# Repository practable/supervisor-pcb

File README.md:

# Remote Labs Supervisor PCB V1.2
NOTE: This project has been continued in a new location, please see: [rl-supervisor-two](https://github.com/practable/rl-supervisor-two) for the latest version of this project

## Project Brief - [Remote Labs Supervisor PCB V1.2]
Design a PCB to provide power to remote labs experiments, which involve students programming microcontrollers remotely. PCB should also provide a supervisory role, blocking actuation of experimental hardware if it is likely to cause damage to the equipment. <br> <br>

This allows students to upload their own code to a bare bones microcontroller, without risk of causing hardware damage or unsafe conditions. <br>

# Using Remote Labs Supervisor PCB 

_This document is intended to be a useage guide for the Remote Labs Supervisor PCB, and document the different use cases and configurations it is capable of._

For coded examples of the various features please see [PCB Unit Tests](https://github.com/ImogenWren/RemoteLabs_Supervisor_PCB/tree/main/Verification%20Tests/PCB%20Unit%20Tests), which contains
arduino code firmware used during testing all hardware features of the PCB.

For the purposes of this document, it is assumed that the Motherboard PCB is populated with both Arduino Nano IoT 33 Daughterboards __(A1 & A2)__, with shift registers installed, and NOT the bare bones SAMD21 MCU.
A seperate document will be provided for cases in which SAMD21 MCUs are mounted to the motherboard directly.

### Pin Naming and Shift Registers

_All MCU pins will be referenced by the Arduino Pin Numbers in this document. 
Additional pins are sourced via Shift Registers attached to each MCU.
Shift Register pins are labelled as Q0 - Q7.
Both MCU connections to their independent shift registers are detailed below._

MCU Pin |  Shift Register Function 	|
---		| ---						|
D8		| LATCH	(Write to Register)	|
D11		| MOSI (Data)				|
D13		| SCK						|

_Complete pinout diagrams for both MCUs and Shift Registers can be found at the bottom of this document_

### Powering the System

The System should be provided 12v DC power via the yellow XT60 connector __J3__. The system is specified to draw a maximum of ~ 8A depending on experiment configuration, ensure that power supply selected is sufficient for specific use case.

Diode D6 (Blue) will light to show correct polarity power is provided to input.
Diode D7 (Orange) will light to show 3V3 DC power is available to microcontrollers and periferal devices.

Motherboard has reverse polarity protection, however care should be taken to ensure correct orientation of power input. - NOTE: Currently missing protection diode- awaiting delivery

### Programming the MCUs

Each MCU, supervisor and student are able to be programmed via the USB connector on the daughterboard, or via UART using the 5 pin headers __J26 Student_Prog_Header__, and __J1 Super_Prog_header__.

For UART Programming, a hat is provided for raspi GPIO pins. 5 pin cable should be connected from Raspi hat to UART Programming connector on motherboard.

__The USB connectors mounted to the __Motherboard__ should not be used if Arduino Development boards are installed, and are UNTESTED for use with bare bones MCUs installed__

-----

## Use Case 1 [Spinner Experiment]

_In this configuration the following modules should be mounted to the motherboard:_

- Infineon DC Motor Control Shield - A3

_In this configuration the following external hardware should be connected as follows:_

- DC Motor, wired to the OUTER two pins on __J18 DC Motor Output__
- Optical Encoder, plugged into __J25 Optical Encoder__

### Using the DC Motor

DC Motor PWM is routed to Infineon DC Motor Controller module via the following logic:

If MOTOR_DIR_A is driven HIGH, PWM is routed from STUDENT_MOTOR_PWM or SUPERVISOR_MOTOR_PWM to MOTOR_OUT_1
If MOTOR_DIR_B is driven HIGH, PWM is routed from STUDENT_MOTOR_PWM or SUPERVISOR_MOTOR_PWM to MOTOR_OUT_2

Care must be taken to avoid driving MOTOR_DIR_A and MOTOR_DIR_B to HIGH at the same time as this will cause shoot through.

In Order to avoid shoot through condition, Student does not have direct input to MOTOR_DIR_A or MOTOR_DIR_B. These outputs are spoofed via the Supervisor MCU.

The MCU able to pass PWM signal to Motor Control Module is selected by MCU_MOTOR_SELECT pin. When HIGH - STUDENT_MOTOR_PWM is active, when LOW - SUPERVISOR_MOTOR_PWM is active.

In order to enable the DC Motor Control Module, OUT_M_ENABLE must also be set HIGH. This is routed from either MCU using the same logic as above, when MCU_MOTOR_SELECT is HIGH, ENABLE is routed from STUDENT_MOTOR_EN, when it is set LOW, ENABLE is routed from SUPERVISOR_MOTOR_EN.

M_I_SENSE_1 and M_I_SENSE_2 output is buffered and distributed to both MCUs.

### Supervisor MCU

Supervisor MCU uses the following table for DC Motor Control:

MCU 		|Pin 	| Pin Name 		| State 		| Motor Behaviour 		| Notes
---			|---	|---			|---			|---					|---
SUPERVISOR 	|D12 	|MOTOR_DIR_1	| HIGH or LOW	| Sets motor Direction	| IF(D7 == HIGH){D12 MUST = LOW)
SUPERVISOR	|D7		|MOTOR_DIR_2	| LOW or HIGH 	| Sets motor Direction 	| IF(D12 == HIGH){D7 MUST = LOW)
SUPERVISOR	|Q0		|DC_MOTOR_EN	| HIGH			| Enables DC Motor Drive|
SUPERVISOR	|Q1		|STUDENT_M_EN	| LOW			| Blocks Student Control, Enables Supervisor Control| 
SUPERVISOR	|A7		|DC_MOTOR_IS1	| ANALOG INPUT	| Current Draw and Fault Condition Detection| 
SUPERVISOR	|A6		|DC_MOTOR_IS2	| ANALOG INPUT	| Current Draw and Fault Condition Detection| 

### Student MCU

Student MCU uses the following table for DC Motor Control: *Note - Student control relys on specific pin configurations of Supervisor MCU*

MCU 		|Pin 	| Pin Name 		| State 		| Motor Behaviour 		| Notes
---			|---	|---			|---			|---					|---
STUDENT 	|D12 	|MOTOR_DIR_1	| HIGH or LOW	| Detected by Supervisor PIN A1	| IF(D7 == HIGH){D12 MUST = LOW)
STUDENT		|D7		|MOTOR_DIR_2	| LOW or HIGH 	| Detected by Supervisor PIN A0	| IF(D12 == HIGH){D7 MUST = LOW)
STUDENT		|Q0		|DC_MOTOR_EN	| HIGH			| Enables DC Motor Drive|
SUPERVISOR	|Q1		|STUDENT_M_EN	| HIGH			| Blocks Supervisor Control, Enables Student Control| 
SUPERVISOR	|A1		|STDNT_DC_M_DIR_1| DIGITAL INPUT| Detects state of Student Direction Pin and Spoofs output if logic != illegal
SUPERVISOR	|A0		|STDNT_DC_M_DIR_2| DIGITAL INPUT| Detects state of Student Direction Pin and Spoofs output if logic != illegal
SUPERVISOR 	|D12 	|MOTOR_DIR_1	| HIGH or LOW	| Sets motor Direction - Spoofed from A1	| 
SUPERVISOR	|D7		|MOTOR_DIR_2	| LOW or HIGH 	| Sets motor Direction - Spoofed from A0	| 
STUDENT		|A7		|DC_MOTOR_IS1	| ANALOG INPUT	| Current Draw and Fault Condition Detection| 
STUDENT		|A6		|DC_MOTOR_IS2	| ANALOG INPUT	| Current Draw and Fault Condition Detection| 

### Using the Optical Encoder

_Optical encoder signals are buffered and provided to both MCUs simaltaniously, therefore getting useful data from Optical Encoder is the same process for both MCUs_

MCUs use the following table for Optical Encoder detection:

MCU 		|Pin 	| Pin Name 		| State 								| Notes
---			|---	|---			|---									|---
Both	 	|D2 	|ENCODER_B		| EXTERNAL INTERRUPT / DIGITAL INPUT	| For best performance, External Interrupt used for edge detection of Encoder waveform
Both		|D3		|ENCODER_A		| EXTERNAL INTERRUPT / DIGITAL INPUT 	| Alternative pin for External Interrupt.
Both		|D4		|ENCODER_INDEX	| DIGITAL INPUT							| Used to track center detent of optical encoder (Untested in software)

-----

## Use Case 2 [Governer Experiment]

In this configuration the following modules should be mounted to the motherboard:

- Infineon DC Motor Control Shield 	- A3
- DRV8825 Stepper Motor Driver		- A4

___DC Motor & Optical Encoder are accessed as Use Case 1 above___

In this configuration the following external hardware should be connected as follows:

- DC Motor, wired to the OUTER two pins on __J18 DC Motor Output__
- Stepper Motor, plugged into __J19 Stepper Motor Output__
- Optical Encoder, plugged into __J25 Optical Encoder__
- Limit Switch, plugged into __J23 limit_switch_A__

### Using the Stepper Motor

Stepper Motor Driver inputs are routed via the following logic:

When MCU_STEP_SELECT is HIGH, inputs are routed from STUDENT MCU. When MCU_STEP_SELECT is LOW, inputs are routed from SUPERVISOR MCU.

STEPP_EN is driven from Supervisor MCU Only, however does not seem to have any effect on stepper motor function. - Requires further investigation.

STEPPR_FAULT output is buffered and distributed to both MCUs.

LIMIT_1 Limit switch input is buffered and distributed to both MCUs.

### Supervisor MCU

Supervisor MCU uses the following table for Stepper Motor Control:

MCU 		|Pin 	| Pin Name 		| State 		| Motor Behaviour 									| Notes
---			|---	|---			|---			|---												|---
SUPERVISOR 	|D6 	|STEPP_STEP		| PULSE			| Motor advances 1 step per pulse					| 
SUPERVISOR	|Q2		|STUDENT_STEP_EN| LOW			| Blocks Student Control, Enables Supervisor Control| 
SUPERVISOR	|Q4		|STEPP_DIR		| HIGH or LOW	| Sets Stepper Motor Direction						|
SUPERVISOR	|Q5		|STEPP_SLP		| HIGH or LOW	| Enables and Sleeps motor to avoid overheating 	| MUST BE HIGH? to enable					| 
SUPERVISOR	|Q6		|STEPP_RST		| HIGH or LOW	| Resets controller board after fault condition 	| MUST BE HIGH? to enable					| 
SUPERVISOR	|Q7		|STEPP_EN		| HIGH or LOW	| Enables motor driver board						| NO DECERNABLE EFFECT? - Needs Testing		| 
SUPERVISOR	|A5		|STEPP_FLT		| DIGITAL INPUT	| Fault reporting from Stepper Control daughterboard| HIGH = NO FAULT, LOW = FAULT 				| 
SUPERVISOR	|A4		|LIMIT_1		| DIGITAL INPUT	| Limit Switch Detection.							| LOW = Switch Pressed 						| 

### Student MCU

Student MCU uses the following table for Stepper Motor Control: *Note - Student control relys on specific pin configurations of Supervisor MCU*

MCU 		|Pin 	| Pin Name 		| State 		| Motor Behaviour 									| Notes
---			|---	|---			|---			|---												|---
STUDENT 	|D6 	|STEPP_STEP		| PULSE			| Motor advances 1 step per pulse					| 
SUPERVISOR	|Q2		|STUDENT_STEP_EN| HIGH			| Enables Student Control, Blocks Supervisor Control| 
STUDENT 	|Q4		|STEPP_DIR		| HIGH or LOW	| Sets Stepper Motor Direction						|
STUDENT		|Q5		|STEPP_SLP		| HIGH or LOW	| Enables and Sleeps motor to avoid overheating 	| MUST BE HIGH? to enable					| 
STUDENT		|Q6		|STEPP_RST		| HIGH or LOW	| Resets controller board after fault condition 	| MUST BE HIGH? to enable					| 
SUPERVISOR	|Q7		|STEPP_EN		| HIGH or LOW	| Enables motor driver board						| NO DECERNABLE EFFECT? - Needs Testing		| 
STUDENT		|A5		|STEPP_FLT		| DIGITAL INPUT	| Fault reporting from Stepper Control daughterboard| HIGH = NO FAULT, LOW = FAULT 				| 
STUDENT		|A4		|LIMIT_1		| DIGITAL INPUT	| Limit Switch Detection.							| LOW = Switch Pressed 						|

#### Additional Stepper Motor Functions

SW1 - Stepper Mode Dipswitches set number of steps per revolution. If UNPOPULATED setting is at MAX RESOLUTION. (1, 1, 1 ) logic for MODE inputs.

-----

## Use Case 3 [Digger Experiment]

In this configuration the following modules should be mounted to the motherboard:

- Infineon DC Motor Control Shield 	- A3

___DC Motor & Optical Encoder are accessed as Use Case 1 above___

In this configuration the following external hardware should be connected as follows:

- DC Motor, wired to the OUTER two pins on __J18 DC Motor Output__
- Optical Encoder, plugged into __J25 Optical Encoder__
- Limit Switch, plugged into __J23 limit_switch_A__
- Servo, plugged into __J20 Servo_A__

In this use case, supervisor must calibrate and track the position of DC motor to avoid equipment collision with self. 

### Supervisor MCU

Supervisor has ultimate control of the Servo PPM output.

Supervisor MCU uses the following table for Servo Motor Control:

MCU 		|Pin 	| Pin Name 		| State 		| Motor Behaviour 									| Notes
---			|---	|---			|---			|---												|---
SUPERVISOR 	|D9 	|SERVO_1		| PPM Output	| PPM Standard sets Servo Position					| 

### Student MCU

Student MCU has no direct output to servo_1, instead supervisor must spoof and constrain output;
given either a PWM signal, or PPM signal from the Student, applied to __Pin A2__ of the supervisorU MCU.

Student MCU uses the following table for Servo Motor Control: *Note - Student control relys on specific pin configurations of Supervisor MCU*

MCU 		|Pin 	| Pin Name 		| State 		| Motor Behaviour 									| Notes
---			|---	|---			|---			|---												|---
STUDENT 	|D9 	|SERVO_1		| PPM or PWM Output	| PPM/PWM used to infer desired position of servo	| 
SUPERVISOR	|A2		|STDNT_SRVO_RX_1| ANALOG INPUT or EXTERNAL INTERRUPT	| Detects infered desired position for servo| 
SUPERVISOR 	|D9 	|SERVO_1		| PPM Output	| PPM Standard sets Servo Position					| 

-----

## Use Case 4 [Pendulum Experiment]

*NOTE: USE CASE UNTESTED*

In this configuration the following modules should be mounted to the motherboard:

- Remote Labs Pendulum PCB Daughterboard - A3

In this configuration the following external hardware should be connected as follows:

- Pendulum Driver, wired to the OUTER two pins on __J18 DC Motor Output__
- Optical Encoder, plugged into __J25 Optical Encoder__

### Supervisor MCU

Supervisor MCU uses the following table for Pendulum Control:

MCU 		|Pin 	| Pin Name 		|Pendulum PCB Pin Name	| State 		| Pendulum Behaviour 	| Notes
---			|---	|---			|---					|---			|---					|---
SUPERVISOR 	|Q0		|DC_MOTOR_EN	| ENABLE	| DIGTAL OUTPUT	| Drive	 |Tried to avoid this being on a shift register - failed can it be moved to another pin? User Thermo A3, and enable
SUPERVISOR 	|D6		|STEPP_STEP		| PENDULUM_PIN_1		| DIGTAL OUTPUT	| Load					|  
SUPERVISOR 	|D12	|DC_MOTOR_DIR_1	| PENDULUM_PIN_7		| DIGTAL OUTPUT	| LED_1 Control			| 	
SUPERVISOR 	|D7		|DC_MOTOR_DIR_2	| PENDULUM_PIN_8		| DIGTAL OUTPUT	| LED_2 Control			| 
SUPERVISOR 	|D9		|SERVO_1		| PENDULUM_PIN_6		| DIGTAL OUTPUT	| LED_3 Control			| 
SUPERVISOR 	|Q1		|STUDENT_M_EN	| PENDULUM_PIN_2		| LOW			| Blocks Student Control, Enables Supervisor Control |
SUPERVISOR	|A7		|DC_MOTOR_IS1	| I_SENSE_1				| ANALOG INPUT	| Current Draw and Fault Condition Detection|  Check which way around these are
SUPERVISOR	|A6		|DC_MOTOR_IS2	| I_SENSE_2				| DIGITAL INPUT	| Current SIGN reporting (+/-)| HIGH = Positive Current, LOW = Negative Current

### Student MCU

Student MCU uses the following table for Stepper Motor Control: *Note - Student control relys on specific pin configurations of Supervisor MCU*

MCU 		|Pin 	| Pin Name 		|Pendulum PCB Pin Name	| State 		| Pendulum Behaviour 	| Notes
---			|---	|---			|---					|---			|---					|---
STUDENT 	|Q0		|DC_MOTOR_EN	| ENABLE	| DIGTAL OUTPUT	| Drive	 |Tried to avoid this being on a shift register - failed can it be moved to another pin? User Thermo A3, and external enable
STUDENT 	|D6		|STEPP_STEP		| PENDULUM_PIN_1		| DIGTAL OUTPUT	| Load					|  
STUDENT  	|A0		|SPARE_0		| PENDULUM_PIN_3		| DIGTAL OUTPUT	| LED_1 Control			| 	
STUDENT  	|A1		|SPARE_1 		| PENDULUM_PIN_4		| DIGTAL OUTPUT	| LED_2 Control			| 
STUDENT  	|A2		|SPARE_2		| PENDULUM_PIN_5		| DIGTAL OUTPUT	| LED_3 Control			| 
SUPERVISOR 	|Q1		|STUDENT_M_EN	| PENDULUM_PIN_2		| HIGH			| Enables Student Control, Blocks Supervisor Control |
STUDENT		|A7		|DC_MOTOR_IS1	| I_SENSE_1				| ANALOG INPUT	| Current Draw and Fault Condition Detection|  Check which way around these are
STUDENT		|A6		|DC_MOTOR_IS2	| I_SENSE_2				| DIGITAL INPUT	| Current SIGN reporting (+/-)| HIGH = Positive Current, LOW = Negative Current

-----

## Additional Features

### WS2812 LEDs

To use WS2812 LED strips with any configuration, the following external hardware should be connected as follows:

- WS2821B LED Strip, connected to __J24 WS2812B LEDs__

__Supervisor MCU__ uses the following table for WS2812B LED Control.

MCU 		|Pin 	| Pin Name 		| State 		| Use			 				| Notes
---			|---	|---			|---			|---							|---
SUPERVISOR 	|D5 	|PIXEL_DATA		| DIGITAL OUTPUT| Sets LED Colour & Brightness	|
SUPERVISOR	|Q3		|STUDENT_PIXEL_EN| LOW			| Blocks Student Control, Enables Supervisor Control		|

__Student MCU__ uses the following table for WS2812B LED Control.: *Note - Student control relys on specific pin configurations of Supervisor MCU*

MCU 		|Pin 	| Pin Name 		| State 		| Use			 				| Notes
---			|---	|---			|---			|---							|---
STUDENT		|D5 	|PIXEL_DATA		| DIGITAL OUTPUT| Sets LED Colour & Brightness	|
SUPERVISOR	|Q3		|STUDENT_PIXEL_EN| HIGH			| Enables Student Control, Blocks Supervisor Control		|

### Power Output Connectors

| Voltage/Bus 		| Purpose/Name	| Component Number 	| Connector Type 	| Current Considerations 	|
|---				|---			|---				|---				|---						|
| 12V				| 12V_DC		|		J30			| Screw Terminal	| Unregulated ~8A Max(For entire Bus)|
| 12V				| Strip Lighting| 		J4			| Molex				| Unregulated ~8A Max(For entire Bus)|
| 12V       		| DC MOTOR PWR	|		J16			| Screw Terminal	| Unregulated ~8A Max(For entire Bus)|
| 5V_DC_LED			| 5V_DC_LED		| 		J6			| Screw Terminal	| 1A Total. Regulated	|
| 5V_DC_RPI			| 5V_DC Spare	| 		J31			| Screw Terminal	| 2.5A Total. Regulated	|
| 5V_DC_RPI			| USB Power		| 		J5			| USB A Socket x2	| 2.5A Total. Regulated	|

#### Additional Voltage Bus Connections

Additional headers have been provided for:
- 3V3 DC Power Output (1A Max)
- 5V DC Digital Power Output (2 - 2.5A Max, including USB Socket)
- 5V DC Servo Power Output (1A Max)
- 12V DC Bus (Unregulated - 6A Max)

These are intended for future use, fault finding or reconfirging PCBs to perform tasks outside of the specified use cases.

### Thermocouple

__Currently Unavailable due to parts shortages__

To use Thermocouple Input with any configuration, the following external hardware should be connected as follows:

- K-Type Thermocouple, connected to __J22 Thermocouple__ connector.

__Thermocouple input __J22 Thermocouple__ requires IC __U19 AD8497__ To be populated. (UNTESTED)__

Analog voltage is buffered and distributed to both MCUs, __Pin A3__

## Pinout Diagrams

_MCU and Shift Register Pinout diagrams_

##### Supervisor MCU

##### Student MCU

## CAD Renders

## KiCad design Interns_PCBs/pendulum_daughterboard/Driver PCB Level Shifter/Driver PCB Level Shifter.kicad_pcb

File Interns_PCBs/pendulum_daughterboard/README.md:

# Pendulum Driver Daughterboard

The task is to design and fabricate a drop in replacement for the motor driver board on the new remote labs PCB. The original daughterboard is the Infineon motor control shield:
  https://uk.rs-online.com/web/p/shields-for-arduino/

The new PCB will be driving the pendulum experiment, the circuit and experiment is documented in this github repo:
https://github.com/practable/penduino

RL supervisor PCB repo found at:
https://github.com/ImogenWren/RemoteLabs_Supervisor_PCB

### Schematic Showing connections to motherboard

I have created a folder for the pendulum daughterboard, if you could keep all the KiCAD files and any notes you make in this folder. Part of the reasoning of this project is “showing our working” so documenting any design decisions you make, current draw calculations, trace sizes etc would be valuable.

The new daughterboard needs to fit into the slot for the old daughterboard, and must match its pinout. We have 3 digital inputs available to the daughterboard, ENABLE, IN_1 and IN_2 and 2 Analog outputs from the daughterboard. The analog outputs go through a set of buffers to feed the ADC pins on each MCU, and both have a 470r resistor to GND. 

On the schematic it shows 4 digital inputs, so I would have a quick chat with Tim Drysdale (CCed In) and ask him if we can tie the two LEDs to the drive and the load pin. This means we would have 2 digital inputs, and one spare. Don’t worry about the encoder as that plugs directly into the motherboard and doesn’t need any additional work.

I don’t know if it is required, but it might be worthwhile thinking about adding some kind of current sensing to the daughterboard which can be output on the analog pins. This could be via a current sense IC, or some other method. It would likely need to measure current through the coil in both directions, but this is a stretch goal. The important part is just replicating the function of the existing circuit. Whatever method is chosen, make sure that the parts to complete are available and in stock from UK suppliers.

Power input into the daughterboard – unfortunately I didn’t think of putting 5v on any of the spare pins, however there is a 5v header on the motherboard, so we will run a wire from here into a large 5v Vin pin on your daughterboard. The coil connections will come out on 2 large pads, like the motor driver board and this will be wired to the screw terminals on the motherboard. These are shown as dotted lines on the picture above.

Ideally this should be a 2 layer board to allow us to fabricate a prototype in house.

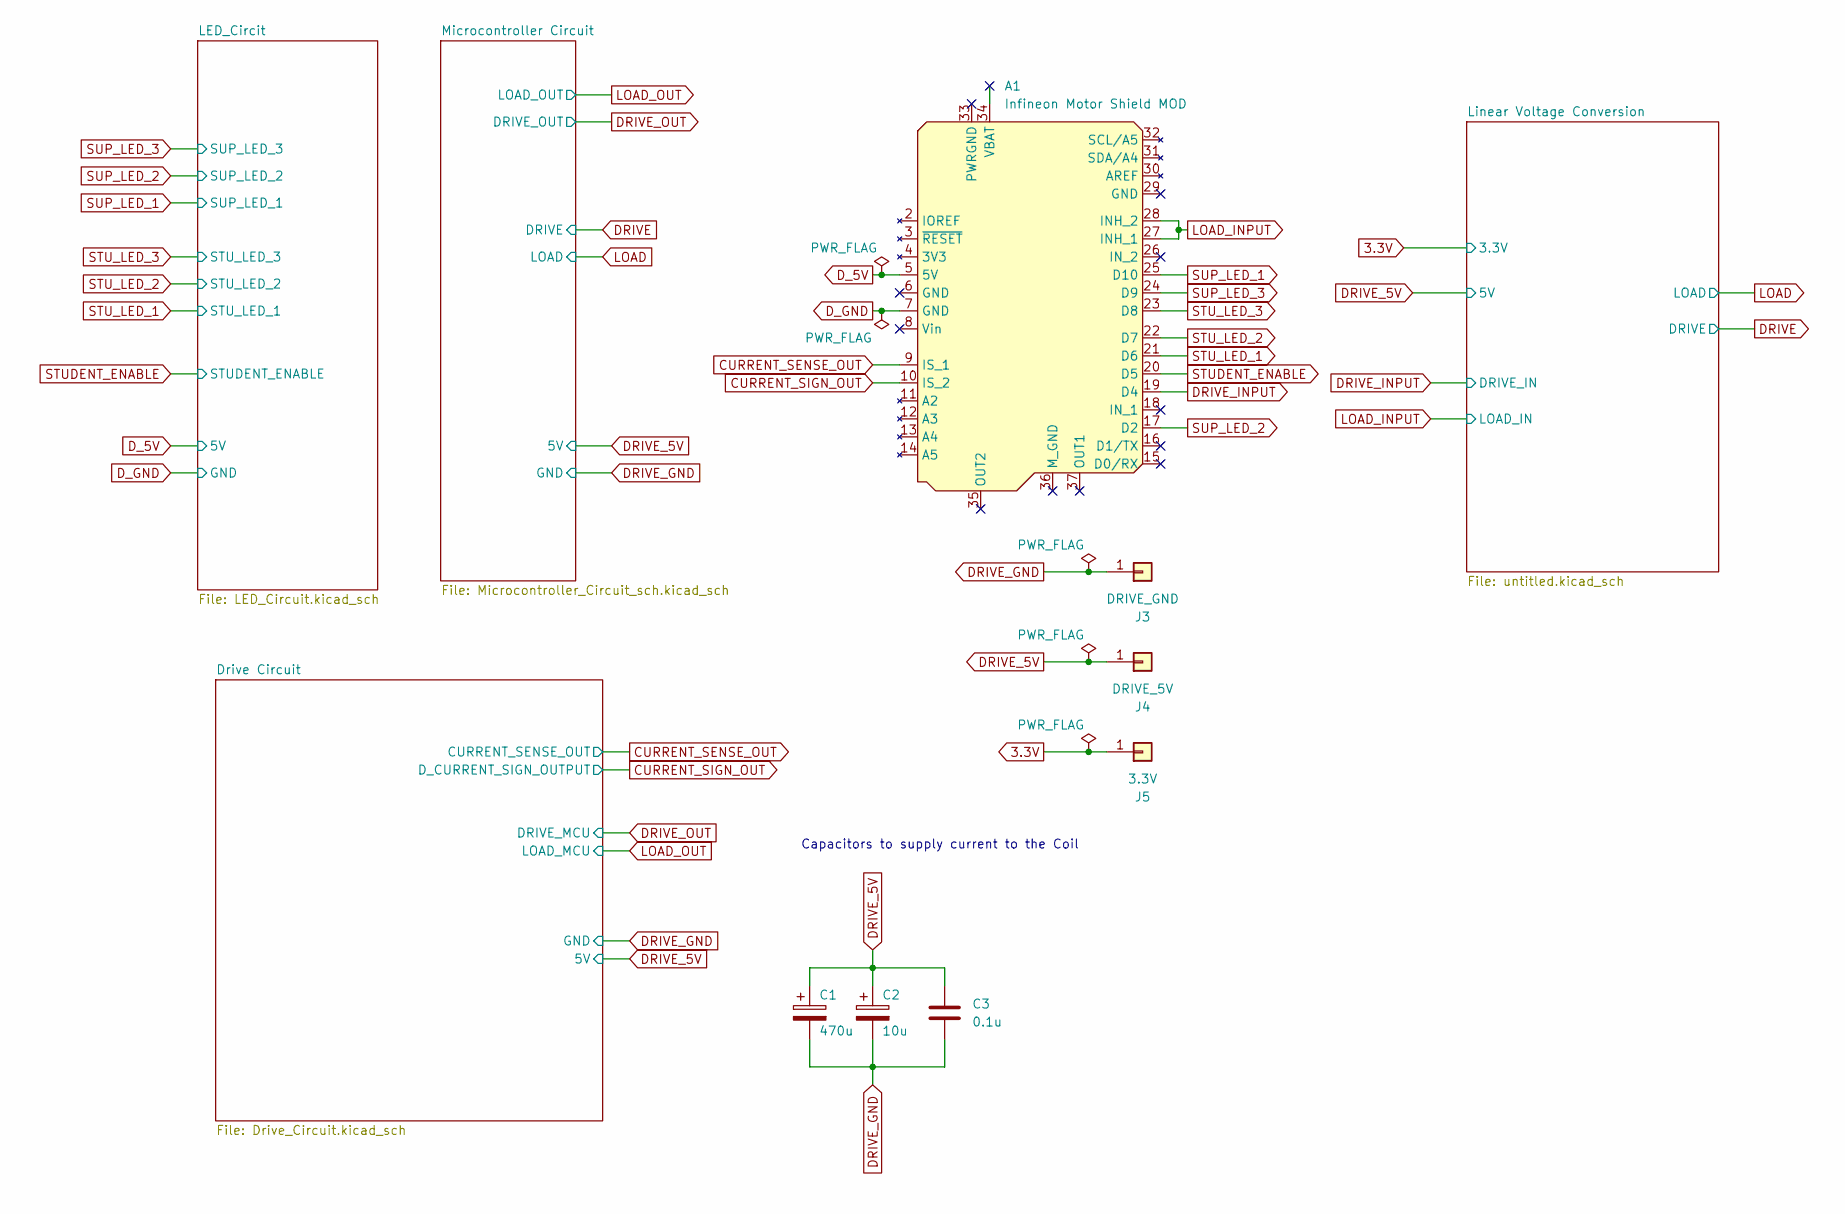
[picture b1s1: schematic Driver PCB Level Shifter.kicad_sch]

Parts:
A1: Infineon Motor Shield MOD; Infineon Motor Sheild hiddenPins
C1: 470u; C_Elec_8x10.2
C2: 10u; CP_Elec_3x5.3
C3: 0.1u; C_0805_2012Metric_Pad1.18x1.45mm_HandSolder
J3: DRIVE_GND; Pin_D1.3mm_L11.0mm
J4: DRIVE_5V; Pin_D1.3mm_L11.0mm
J5: 3.3V; Pin_D1.3mm_L11.0mm

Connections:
3.3V: J5.1; also elsewhere on the board
CURRENT_SENSE_OUT: A1.9 (IS_1); also elsewhere on the board
CURRENT_SIGN_OUT: A1.10 (IS_2); also elsewhere on the board
DRIVE_5V: C1.1, C2.1, C3.1, J4.1; also elsewhere on the board
DRIVE_GND: C1.2, C2.2, C3.2, J3.1; also elsewhere on the board
DRIVE_INPUT: A1.19 (D4); also elsewhere on the board
D_5V: A1.5 (5V); also elsewhere on the board
D_GND: A1.7 (GND); also elsewhere on the board
LOAD_INPUT: A1.27 (INH_1), A1.28 (INH_2); also elsewhere on the board
STUDENT_ENABLE: A1.20 (D5); also elsewhere on the board
STU_LED_1: A1.21 (D6); also elsewhere on the board
STU_LED_2: A1.22 (D7); also elsewhere on the board
STU_LED_3: A1.23 (D8); also elsewhere on the board
SUP_LED_1: A1.25 (D10); also elsewhere on the board
SUP_LED_2: A1.17 (D2); also elsewhere on the board
SUP_LED_3: A1.24 (D9); also elsewhere on the board

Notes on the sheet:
Capacitors to supply current to the Coil

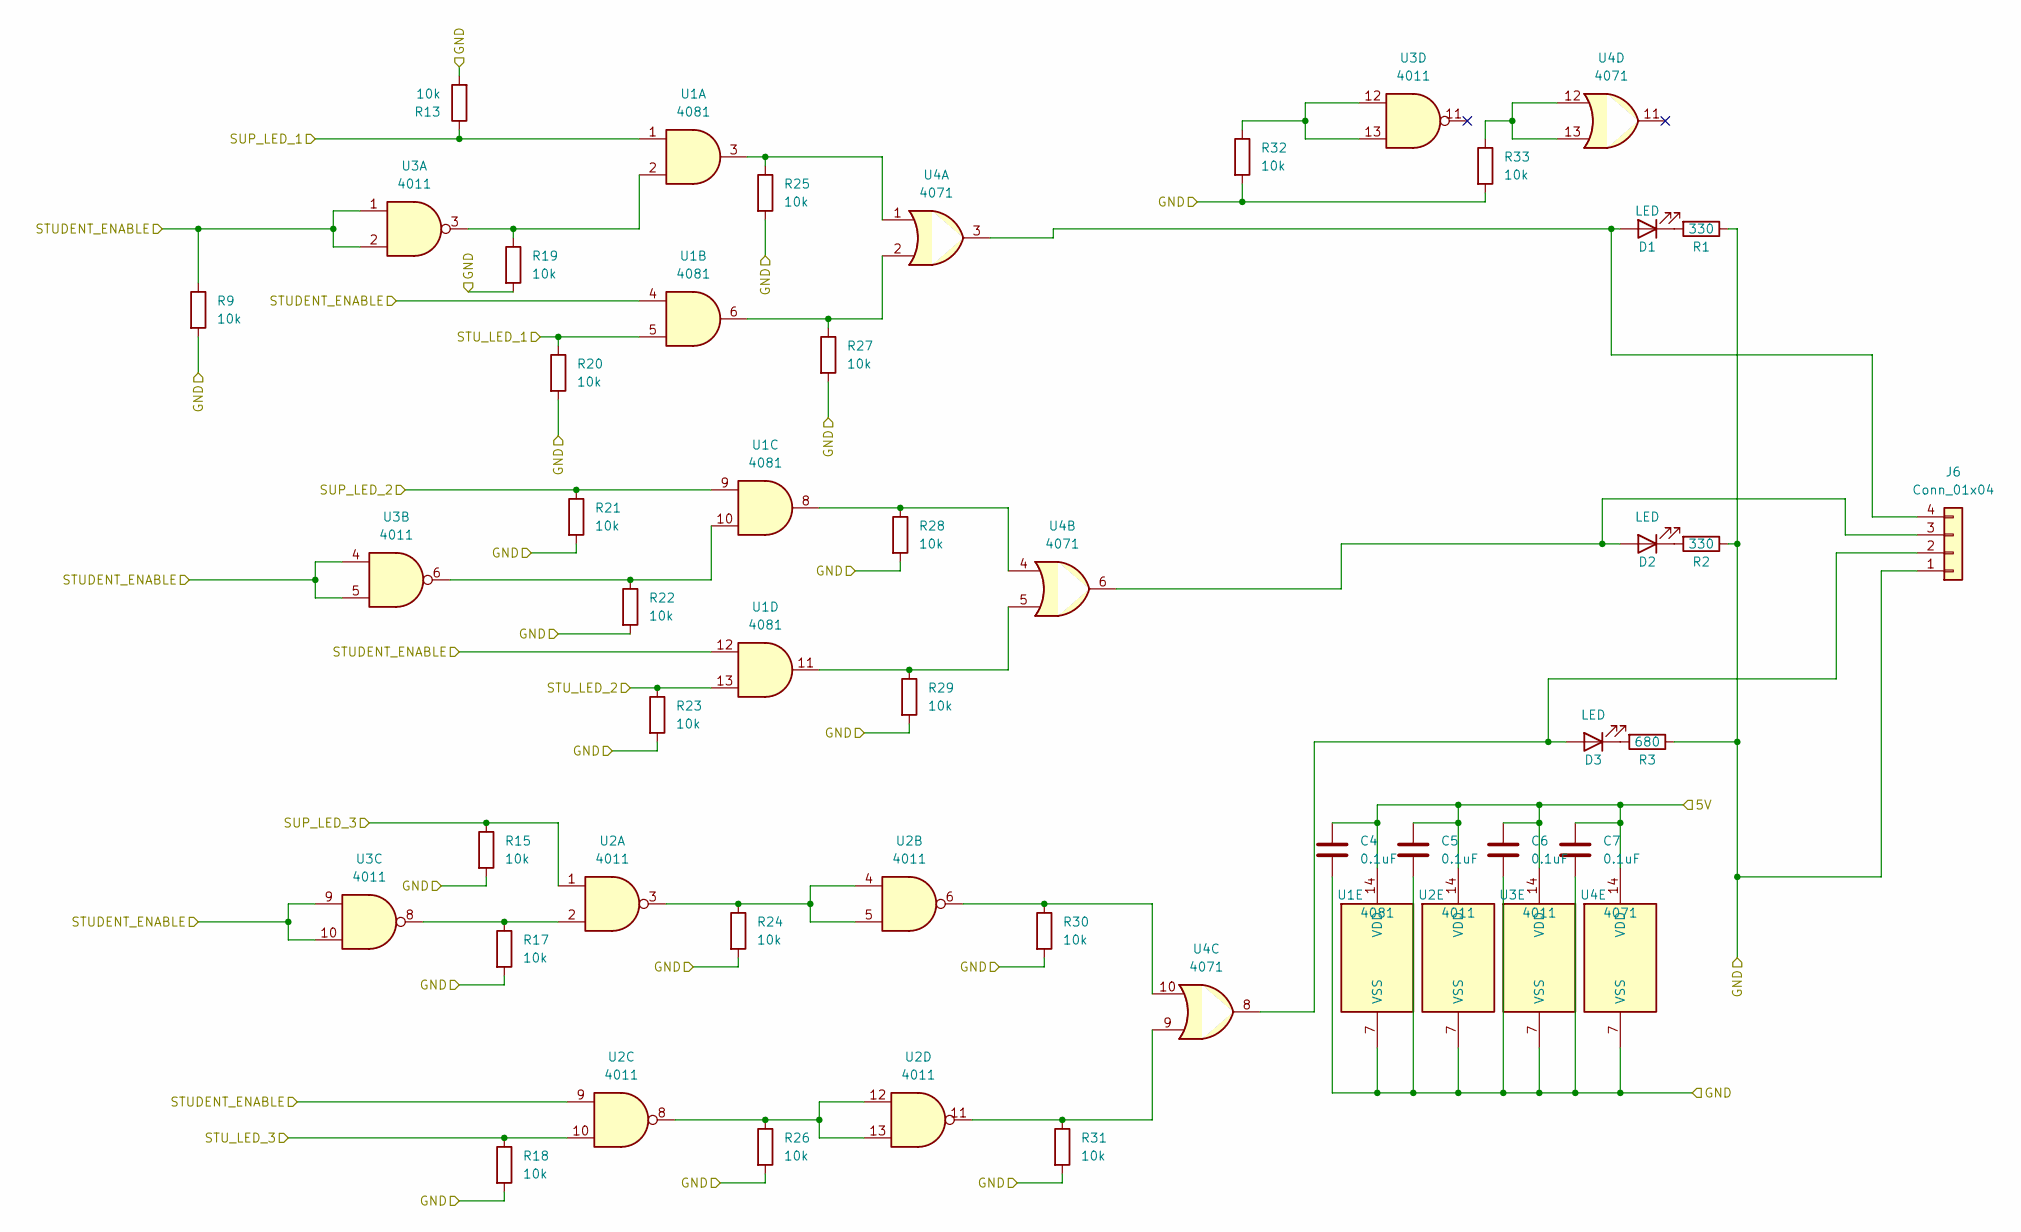
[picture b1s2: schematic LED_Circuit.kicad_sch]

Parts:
C4, C5, C6, C7: 0.1uF; C_0805_2012Metric_Pad1.18x1.45mm_HandSolder
D1, D2, D3: LED; LED_0805_2012Metric_Pad1.15x1.40mm_HandSolder
J6: Conn_01x04; PinHeader_1x04_P2.54mm_Vertical
R1, R2: 330; R_0805_2012Metric_Pad1.20x1.40mm_HandSolder
R3: 680; R_0805_2012Metric_Pad1.20x1.40mm_HandSolder
R9, R13, R15, R17, R18, R19, R20, R21, R22, R23, R24, R25, R26, R27, R28, R29, R30, R31, R32, R33: 10k; R_0805_2012Metric_Pad1.20x1.40mm_HandSolder
U1: 4081; SOIC127P600X175-14N
U2, U3: 4011; SOIC127P600X175-14N
U4: 4071; SOIC127P600X175-14N

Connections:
D_5V: C4.1, C5.1, C6.1, C7.1, U1.14 (VDD), U2.14 (VDD), U3.14 (VDD), U4.14 (VDD); also elsewhere on the board
D_GND: C4.2, C5.2, C6.2, C7.2, J6.1, R1.1, R2.1, R3.1, R9.2, R13.2, R15.2, R17.2, R18.2, R19.2, R20.2, R21.2, R22.2, R23.2, R24.2, R25.2, R26.2, R27.2, R28.2, R29.2, R30.2, R31.2, R32.2, R33.2, U1.7 (VSS), U2.7 (VSS), U3.7 (VSS), U4.7 (VSS); also elsewhere on the board
unnamed: D1.1 (K), R1.2
unnamed: D1.2 (A), J6.4, U4.3
unnamed: D2.1 (K), R2.2
unnamed: D2.2 (A), J6.3, U4.6
unnamed: D3.1 (K), R3.2
unnamed: D3.2 (A), J6.2, U4.8
unnamed: R17.1, U2.2, U3.8
unnamed: R19.1, U1.2, U3.3
unnamed: R22.1, U1.10, U3.6
unnamed: R24.1, U2.3, U2.4, U2.5
unnamed: R25.1, U1.3, U4.1
unnamed: R26.1, U2.8, U2.12, U2.13
unnamed: R27.1, U1.6, U4.2
unnamed: R28.1, U1.8, U4.4
unnamed: R29.1, U1.11, U4.5
unnamed: R30.1, U2.6, U4.10
unnamed: R31.1, U2.11, U4.9
unnamed: R32.1, U3.12, U3.13
unnamed: R33.1, U4.12, U4.13
STUDENT_ENABLE: R9.1, U1.4, U1.12, U2.9, U3.1, U3.2, U3.4, U3.5, U3.9, U3.10; also elsewhere on the board
STU_LED_1: R20.1, U1.5; also elsewhere on the board
STU_LED_2: R23.1, U1.13; also elsewhere on the board
STU_LED_3: R18.1, U2.10; also elsewhere on the board
SUP_LED_1: R13.1, U1.1; also elsewhere on the board
SUP_LED_2: R21.1, U1.9; also elsewhere on the board
SUP_LED_3: R15.1, U2.1; also elsewhere on the board

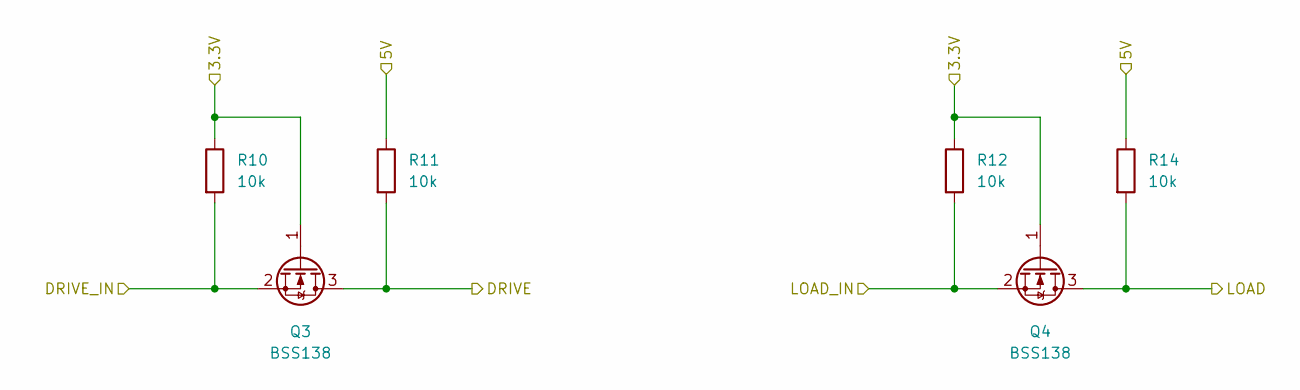
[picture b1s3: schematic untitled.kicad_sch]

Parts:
Q3, Q4: BSS138; SOT-23
R10, R11, R12, R14: 10k; R_0805_2012Metric_Pad1.20x1.40mm_HandSolder

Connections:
3.3V: Q3.1 (G), Q4.1 (G), R10.1, R12.1; also elsewhere on the board
DRIVE: Q3.3 (D), R11.2; also elsewhere on the board
DRIVE_5V: R11.1, R14.1; also elsewhere on the board
DRIVE_INPUT: Q3.2 (S), R10.2; also elsewhere on the board
LOAD: Q4.3 (D), R14.2; also elsewhere on the board
LOAD_INPUT: Q4.2 (S), R12.2; also elsewhere on the board

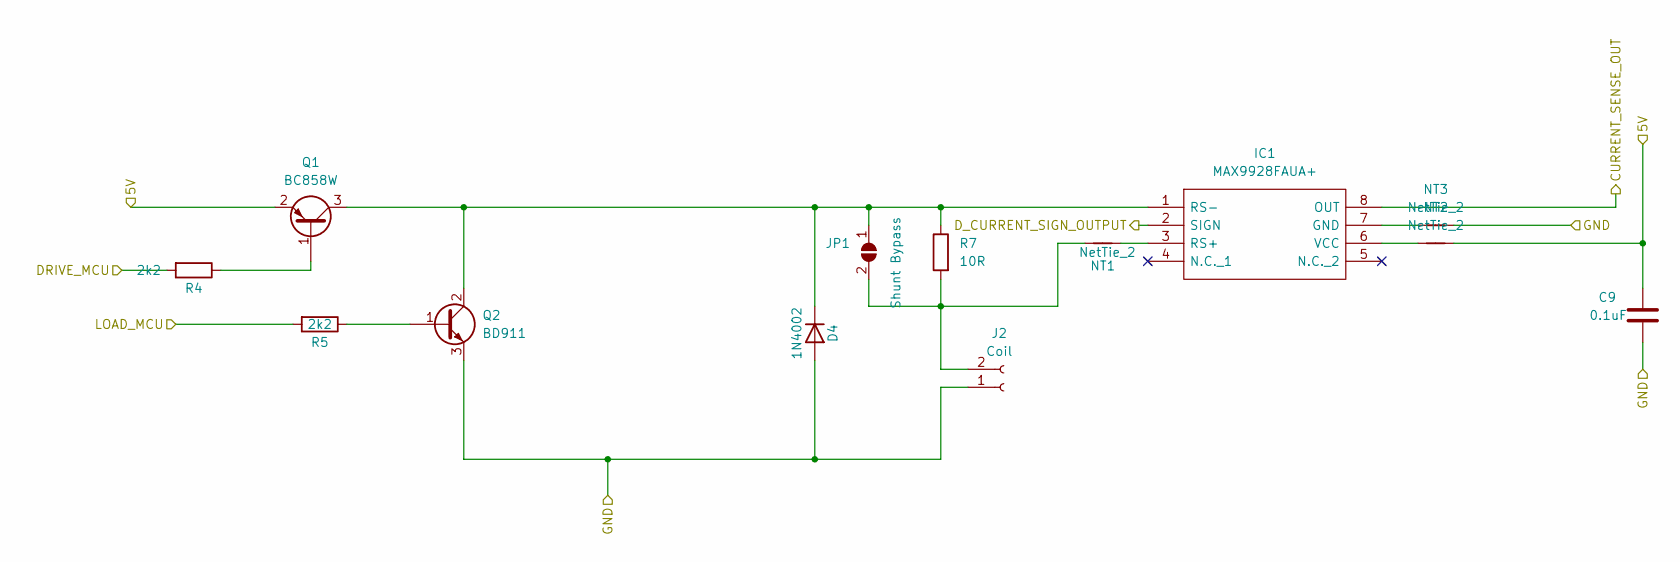
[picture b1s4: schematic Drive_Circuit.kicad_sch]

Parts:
C9: 0.1uF; C_0805_2012Metric_Pad1.18x1.45mm_HandSolder
D4: 1N4002; D_T-1_P5.08mm_Horizontal
IC1: MAX9928FAUA+; SOP65P490X110-8N; Manufacturer_Part_Number MAX9928FAUA+; Mouser Part Number 700-MAX9928FAUA
J2: Coil; RSPROPenduinoTerminal
JP1: Shunt Bypass; SolderJumper-2_P1.3mm_Open_Pad1.0x1.5mm
NT1, NT2, NT3: NetTie_2; NetTie-2_SMD_Pad0.5mm
Q1: BC858W; SOT-23
Q2: BD911; SOT-23
R4, R5: 2k2; R_0805_2012Metric_Pad1.20x1.40mm_HandSolder
R7: 10R; R_0805_2012Metric_Pad1.20x1.40mm_HandSolder

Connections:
CURRENT_SENSE_OUT: IC1.8 (OUT); also elsewhere on the board
CURRENT_SIGN_OUT: IC1.2 (SIGN); also elsewhere on the board
DRIVE_5V: C9.1, NT2.2, Q1.2 (E); also elsewhere on the board
DRIVE_GND: C9.2, D4.1 (A), J2.1, NT3.2, Q2.3 (E); also elsewhere on the board
DRIVE_OUT: R4.2; also elsewhere on the board
LOAD_OUT: R5.2; also elsewhere on the board
unnamed: D4.2 (K), IC1.1 (RS-), JP1.1 (A), Q1.3 (C), Q2.2 (C), R7.1
unnamed: IC1.3 (RS+), NT1.2
unnamed: IC1.6 (VCC), NT2.1
unnamed: IC1.7 (GND), NT3.1
unnamed: J2.2, JP1.2 (B), NT1.1, R7.2
unnamed: Q1.1 (B), R4.1
unnamed: Q2.1 (B), R5.1

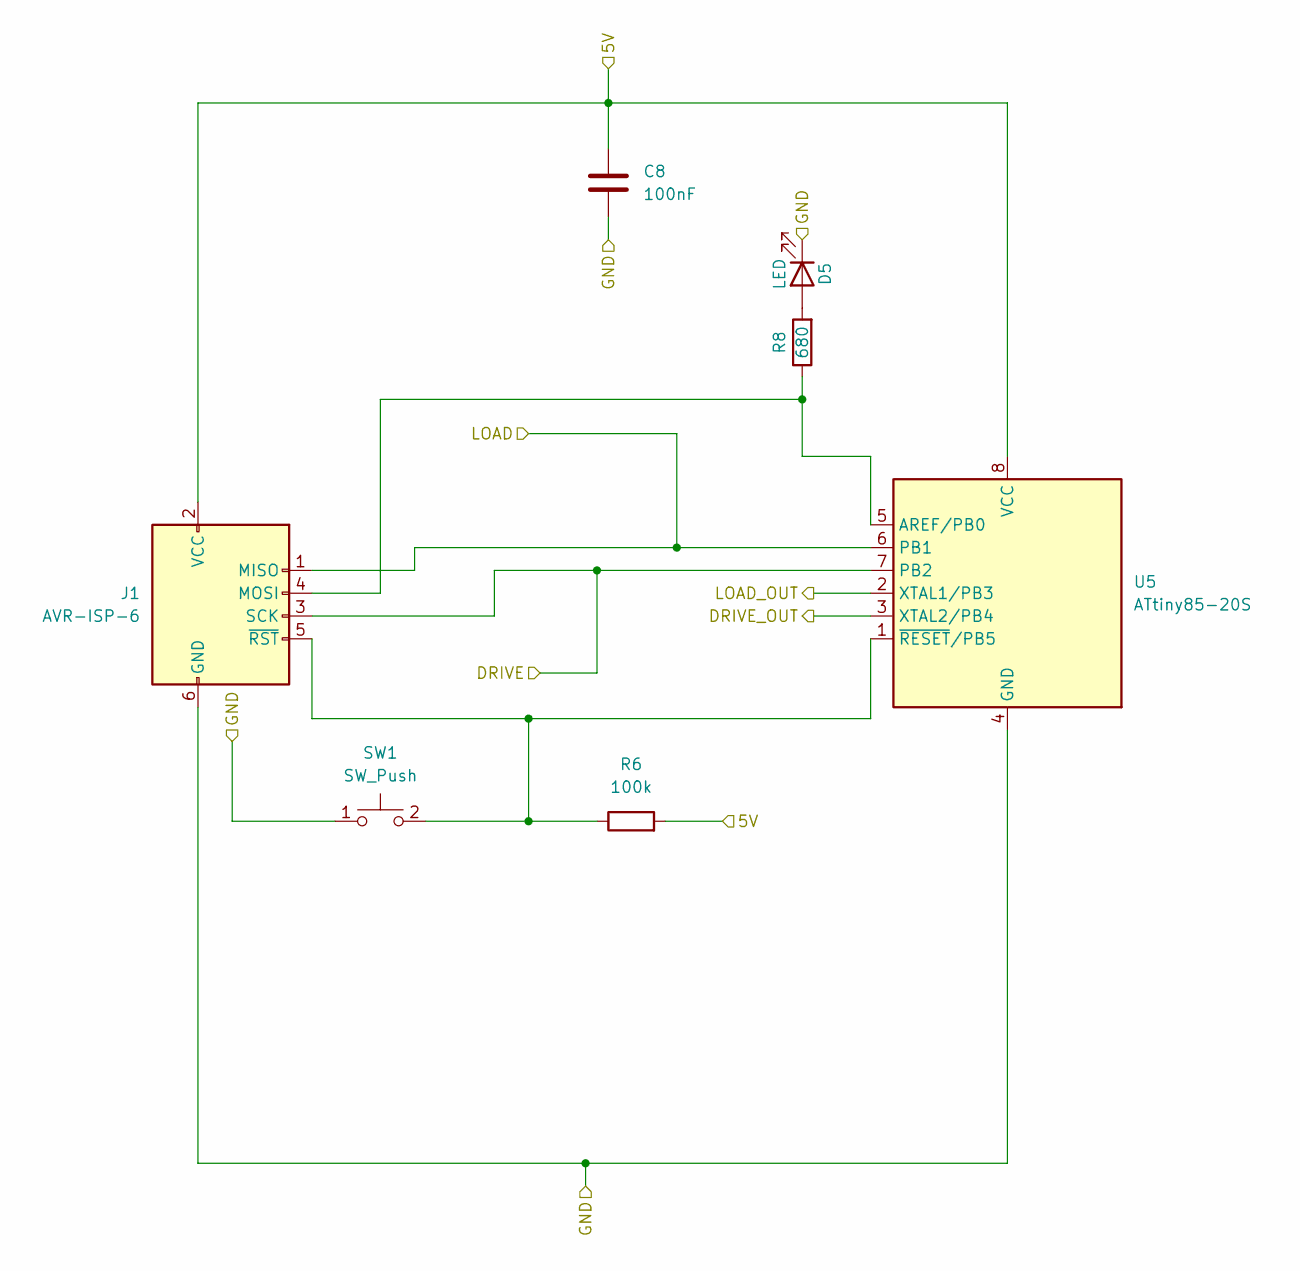
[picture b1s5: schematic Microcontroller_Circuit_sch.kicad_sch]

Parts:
C8: 100nF; C_0805_2012Metric_Pad1.18x1.45mm_HandSolder
D5: LED; LED_0805_2012Metric_Pad1.15x1.40mm_HandSolder
J1: AVR-ISP-6; PinHeader_2x03_P2.54mm_Vertical
R6: 100k; R_0805_2012Metric_Pad1.20x1.40mm_HandSolder
R8: 680; R_0805_2012Metric_Pad1.20x1.40mm_HandSolder
SW1: SW_Push; 13019319
U5: ATtiny85-20S; SOIC-8W_5.3x5.3mm_P1.27mm

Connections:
DRIVE: J1.3 (SCK), U5.7 (PB2); also elsewhere on the board
DRIVE_5V: C8.1, J1.2 (VCC), R6.2, U5.8 (VCC); also elsewhere on the board
DRIVE_GND: C8.2, D5.1 (K), J1.6 (GND), SW1.1, U5.4 (GND); also elsewhere on the board
DRIVE_OUT: U5.3 (XTAL2/PB4); also elsewhere on the board
LOAD: J1.1 (MISO), U5.6 (PB1); also elsewhere on the board
LOAD_OUT: U5.2 (XTAL1/PB3); also elsewhere on the board
unnamed: D5.2 (A), R8.2
unnamed: J1.4 (MOSI), R8.1, U5.5 (AREF/PB0)
unnamed: J1.5 (~RST), R6.1, SW1.2, U5.1 (~RESET/PB5)

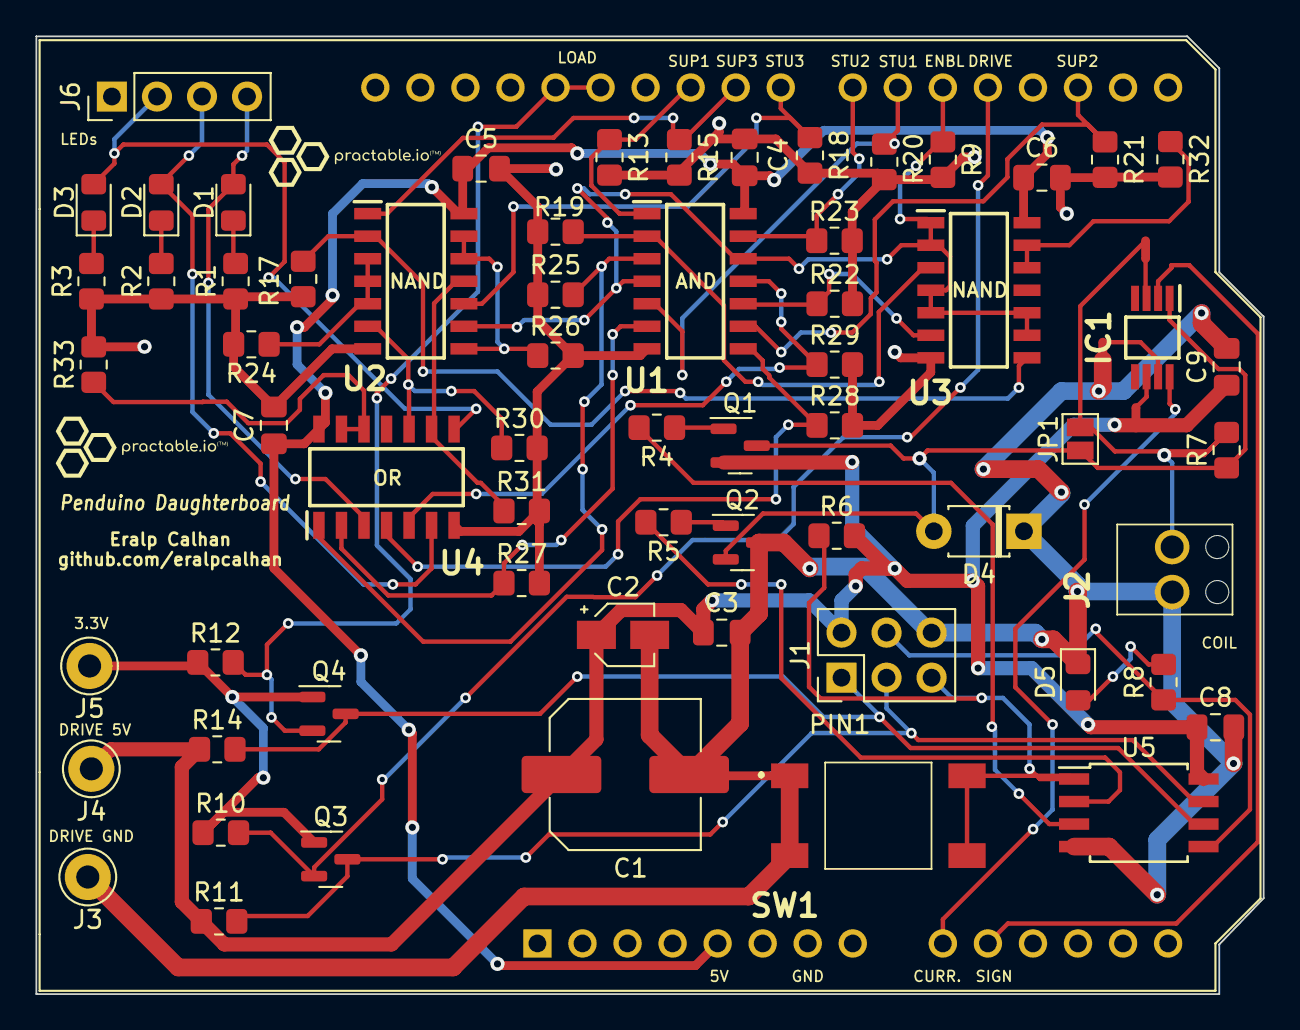
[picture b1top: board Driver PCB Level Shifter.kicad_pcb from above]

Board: 2 copper layers, 69.2 x 54.0 mm, 68 parts (0 on the bottom side), 49 nets.
